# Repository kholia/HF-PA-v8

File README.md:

This work improves upon https://github.com/kholia/HF-PA-v6.

Central idea:

When driven by a Si5351 directly, the output of BS170 is mere 7 to 8 Vpp at 28
MHz.

When driven by a hex-inverter, the output of BS170 easily reaches 13 Vpp at 28
MHz.

This higher BS170 driver output is likely to produce better results (more power
and efficiency) from the IRF510 final @ 28 MHz.

Long-term TODO: Convert all components to SMD. The legs of the THT components
can be bent and fit on top of SMD pads!

- Pots - Bend legs

- Hex-inverter - Get the SMD version of the SN74ACT04N IC.

- BS170 - Bend legs

- Toroids - Bent the leads, stabilize using RTV silicone glue

- Electrolytic caps - Use SMD electrolytic caps

- Diode - Use SMD diode or bend the leads

- PTT - Use SMT pin header, if available?

With this technique the bottom of the PCB will be all ground. This makes
mounting the heat sink an easier problem.

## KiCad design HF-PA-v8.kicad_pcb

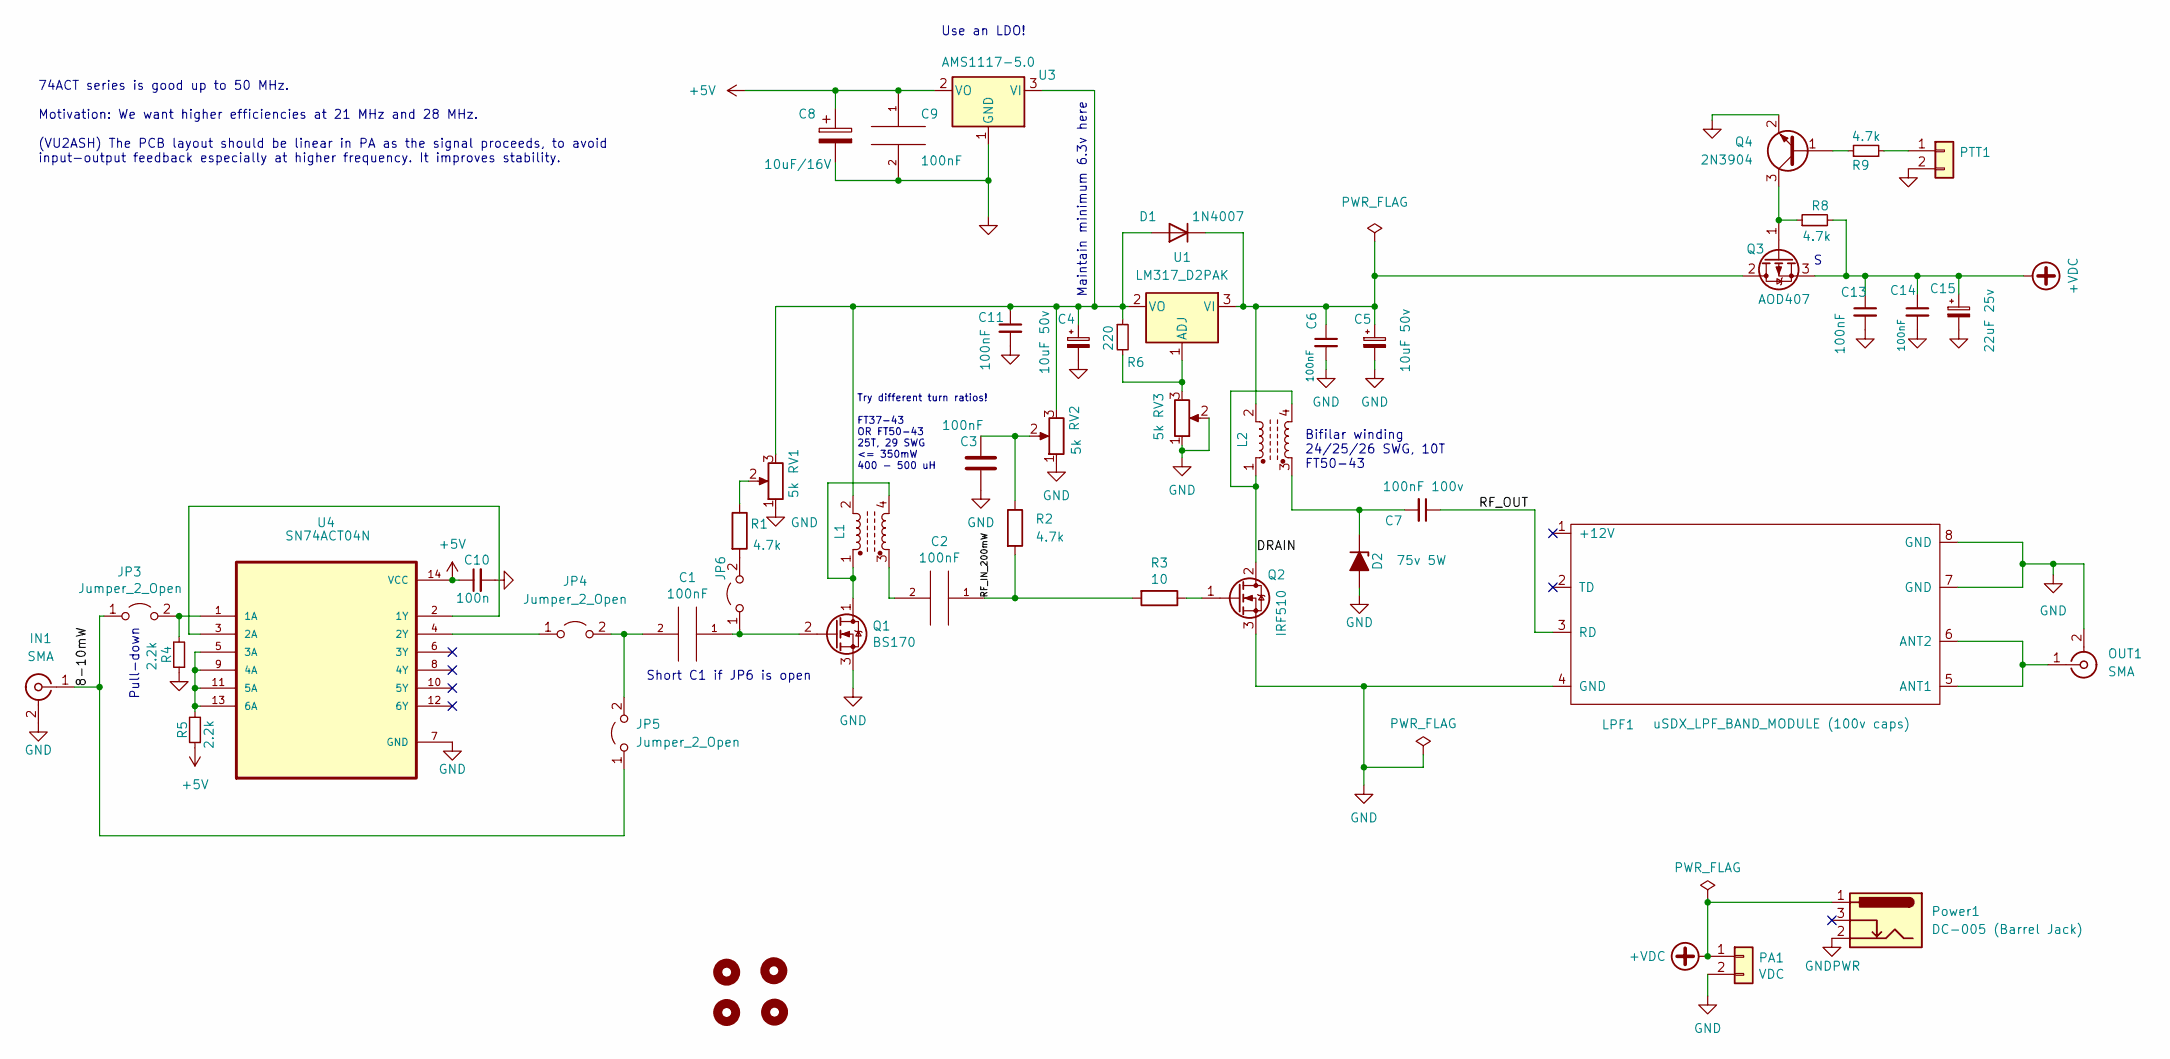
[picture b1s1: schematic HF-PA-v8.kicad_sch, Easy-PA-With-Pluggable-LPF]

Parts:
C1, C2, C3, C6, C9, C11, C13, C14: 100nF; C_1206_3216Metric_Pad1.33x1.80mm_HandSolder
C4, C5: 10uF 50v; CP_Radial_D5.0mm_P2.50mm
C7: 100nF 100v; C_1206_3216Metric_Pad1.33x1.80mm_HandSolder
C8: 10uF/16V; CP_Radial_D5.0mm_P2.50mm
C10: 100n; C_1206_3216Metric_Pad1.33x1.80mm_HandSolder
C15: 22uF 25v; CP_Radial_D5.0mm_P2.50mm
D1: 1N4007; D_DO-41_SOD81_P10.16mm_Horizontal
D2: 75v 5W; D_DO-201_P5.08mm_Vertical_KathodeUp
H1, H2, H3, H4: MountingHole; MountingHole_3.2mm_M3
IN1: SMA; SMA_Amphenol_901-144_Vertical
JP3, JP4, JP5, JP6: Jumper_2_Open; C_0805_2012Metric_Pad1.18x1.45mm_HandSolder
L1, L2: L_Ferrite_Coupled; FT50-43 Transformer
LPF1: uSDX_LPF_BAND_MODULE (100v caps); uSDX_LPF_Band_Module
OUT1: SMA; SMA_Amphenol_901-144_Vertical
PA1: VDC; PinHeader_1x02_P2.54mm_Vertical
PTT1: PTT; PinHeader_1x02_P2.54mm_Vertical
Power1: DC-005 (Barrel Jack); XKB_DC-005-5A-2.0_Modded
Q1: BS170; PinSocket_1x03_P2.54mm_Vertical
Q2: IRF510; TO-220-3_Horizontal_TabDown
Q3: AOD407; TO-252-2
Q4: 2N3904; SOT-23
R1, R2, R8, R9: 4.7k; R_1206_3216Metric_Pad1.30x1.75mm_HandSolder
R3: 10; R_1206_3216Metric_Pad1.30x1.75mm_HandSolder
R4, R5: 2.2k; R_1206_3216Metric_Pad1.30x1.75mm_HandSolder
R6: 220; R_1206_3216Metric_Pad1.30x1.75mm_HandSolder
RV1, RV2, RV3: 5k; Potentiometer_Runtron_RM-065_Vertical
U1: LM317_D2PAK; TO-263-2
U3: AMS1117-5.0; SOT-223-3_TabPin2
U4: SN74ACT04N; DIP794W45P254L1969H508Q14

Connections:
+5V: C8.1, C9.1, C10.1, R5.1, U3.2 (VO), U4.14 (VCC)
+VDC: C13.1, C14.1, C15.1, PA1.1, Power1.1, Q3.3 (S), R8.2
/8-10mW: IN1.1 (In), JP3.1 (A), JP5.1 (A)
/DRAIN: L2.1, L2.4, Q2.2 (D)
/RF_IN_200mW: C2.1, R2.2, R3.2
/RF_OUT: C7.1, LPF1.3 (RD)
unnamed: C1.1, JP6.1 (A), Q1.2 (G)
unnamed: C1.2, JP4.2 (B), JP5.2 (B)
unnamed: C2.2, L1.3
unnamed: C3.1, R2.1, RV2.2
unnamed: C5.1, C6.1, D1.1 (K), L2.2, Q3.2 (D), U1.3 (VI)
unnamed: C7.2, D2.1 (K), L2.3
unnamed: C4.1, C11.1, D1.2 (A), L1.2, R6.1, RV1.3, RV2.3, U1.2 (VO), U3.3 (VI)
unnamed: JP3.2 (B), R4.2, U4.1 (1A)
unnamed: JP4.1 (A), U4.4 (2Y)
unnamed: JP6.2 (B), R1.2
unnamed: L1.1, L1.4, Q1.1 (D)
unnamed: LPF1.5 (ANT1), LPF1.6 (ANT2), OUT1.1 (In)
unnamed: PTT1.1, R9.2
unnamed: Q2.1 (G), R3.1
unnamed: Q3.1 (G), Q4.3 (C), R8.1
unnamed: Q4.1 (B), R9.1
unnamed: R1.1, RV1.2
unnamed: R5.2, U4.5 (3A), U4.9 (4A), U4.11 (5A), U4.13 (6A)
unnamed: R6.2, RV3.3, U1.1 (ADJ)
unnamed: U4.2 (1Y), U4.3 (2A)

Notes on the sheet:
Maintain minimum 6.3v here
Pull-down
Bifilar winding 24/25/26 SWG, 10T FT50-43
Try different turn ratios! FT37-43 OR FT50-43 25T, 29 SWG <= 350mW 400 - 500 uH
74ACT series is good up to 50 MHz. Motivation: We want higher efficiencies at 21 MHz and 28 MHz. (VU2ASH) The PCB layout should be linear in PA as the signal proceeds, to avoid input-output feedback especially at higher frequency. It improves stability.
Short C1 if JP6 is open
Use an LDO!

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
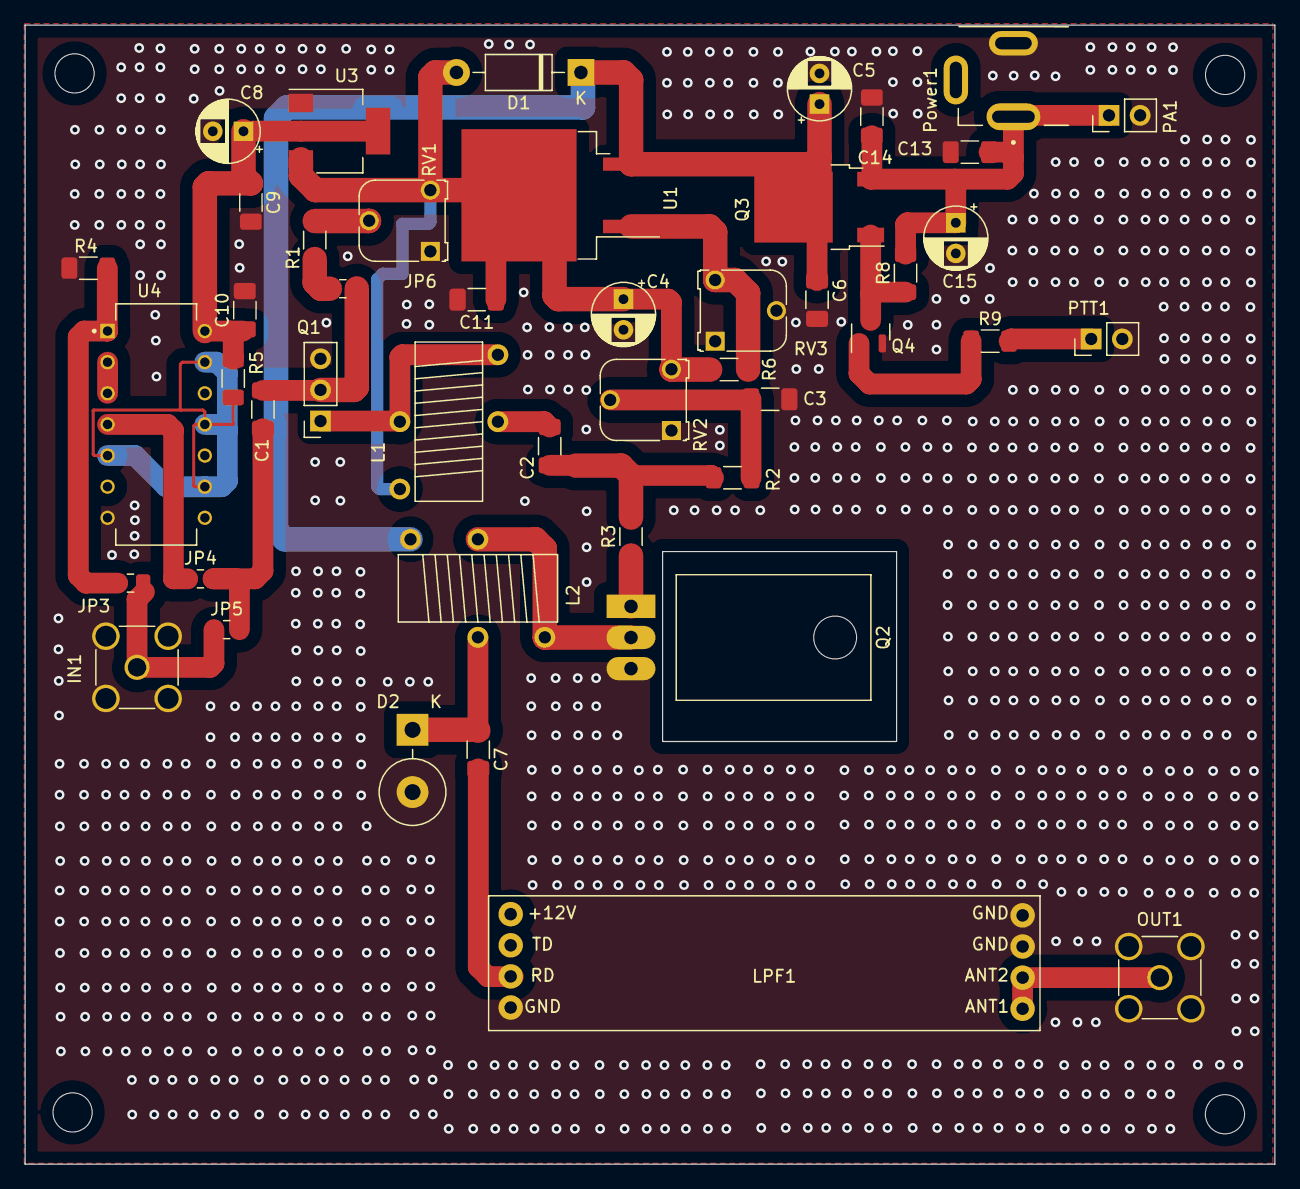
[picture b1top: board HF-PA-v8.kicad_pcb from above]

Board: 2 copper layers, 102.0 x 93.0 mm, 50 parts (0 on the bottom side), 27 nets.

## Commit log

2022-11-20 Initial version
